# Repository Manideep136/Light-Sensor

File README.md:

# Light-Sensor

## Overview

This project is a Light Sensor circuit based on an LDR (Light Dependent
Resistor) and an operational amplifier.

The circuit detects changes in the surrounding light intensity using an LDR.
The changing resistance of the LDR is converted into a voltage variation,
which is then processed by the op-amp circuit.

The schematic and PCB were designed using KiCad.

## Features

- LDR-based light sensing
- Op-amp based signal processing
- Adjustable light detection
- Custom PCB design
- KiCad schematic
- KiCad PCB layout
- Gerber files for PCB manufacturing
- 3D PCB visualization

## How It Works

An LDR (Light Dependent Resistor) changes its resistance depending on the
amount of light falling on it.

- In bright light, the resistance of the LDR decreases.
- In darkness, the resistance of the LDR increases.

The LDR is combined with a resistor to form a voltage divider. The voltage
produced by this divider changes according to the surrounding light level.

This changing voltage is supplied to the op-amp circuit, which processes the
signal and provides the required output.

## Main Components

| Component | Purpose |
|-----------|---------|
| LDR | Detects surrounding light intensity |
| Op-Amp | Processes and compares the sensor voltage |
| Resistors | Voltage division and biasing |
| Capacitors | Filtering and signal stability |
| Potentiometer | Adjusts the detection threshold |
| Connectors | Power and output connections |

## Circuit

The main parts of the circuit are:

1. LDR light sensing section
2. Voltage divider
3. Op-amp section
4. Threshold adjustment
5. Power supply section
6. Output section

## PCB Design

The PCB was designed using **KiCad**.

The design process includes:

1. Creating the schematic
2. Selecting the required components
3. Assigning footprints
4. Creating the PCB layout
5. Placing components
6. Routing PCB tracks
7. Checking the PCB design
8. Running Design Rules Check (DRC)
9. Generating Gerber files
10. Viewing the PCB in 3D

## Software Used

- KiCad
- KiCad Schematic Editor
- KiCad PCB Editor
- KiCad 3D Viewer

## Project Structure

```text
LDR-Light-Sensor/
│
├── doc/
│   ├── Schematic.png
│   ├── Layout.png
│   └── 3D_View.png
│
├── gerber/
│   ├── *.gbr
│   └── *.drl
│
├── LDR Light Sensor.kicad_pro
├── LDR Light Sensor.kicad_sch
├── LDR Light Sensor.kicad_pcb
│
└── README.md

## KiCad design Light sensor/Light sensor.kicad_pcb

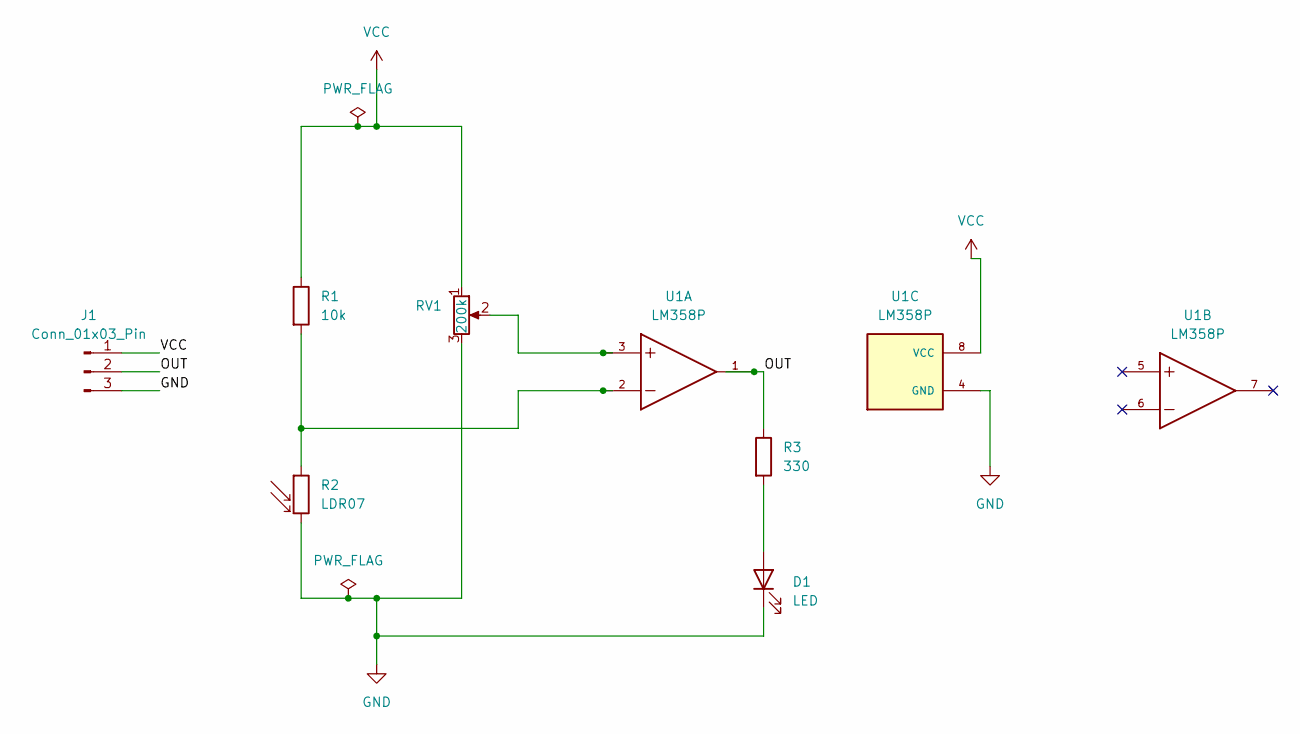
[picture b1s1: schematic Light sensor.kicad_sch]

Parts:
D1: LED; LED_D5.0mm
J1: Conn_01x03_Pin; PinHeader_1x03_P2.54mm_Horizontal
R1: 10k; R_Axial_DIN0204_L3.6mm_D1.6mm_P5.08mm_Horizontal
R2: LDR07; R_LDR_5.1x4.3mm_P3.4mm_Vertical
R3: 330; R_Axial_DIN0204_L3.6mm_D1.6mm_P5.08mm_Horizontal
RV1: 200k; Potentiometer_Bourns_3266W_Vertical
U1: LM358P; DIP794W45P254L959H508Q8; PARTREV FEBRUARY 2021

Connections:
/OUT: J1.2, R3.1, U1.1
GND: D1.1 (K), J1.3, R2.2, RV1.3, U1.4 (GND)
unnamed: D1.2 (A), R3.2
unnamed: R1.2, R2.1, U1.2
unnamed: RV1.2, U1.3
VCC: J1.1, R1.1, RV1.1, U1.8 (VCC)

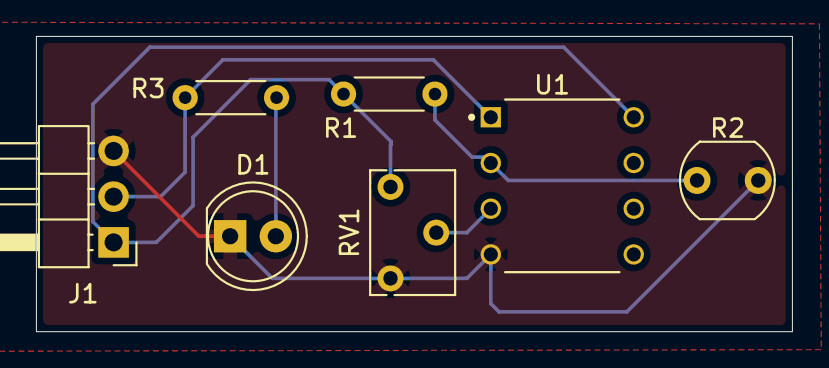
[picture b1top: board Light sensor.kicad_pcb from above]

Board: 2 copper layers, 42.0 x 16.4 mm, 7 parts (0 on the bottom side), 6 nets.
